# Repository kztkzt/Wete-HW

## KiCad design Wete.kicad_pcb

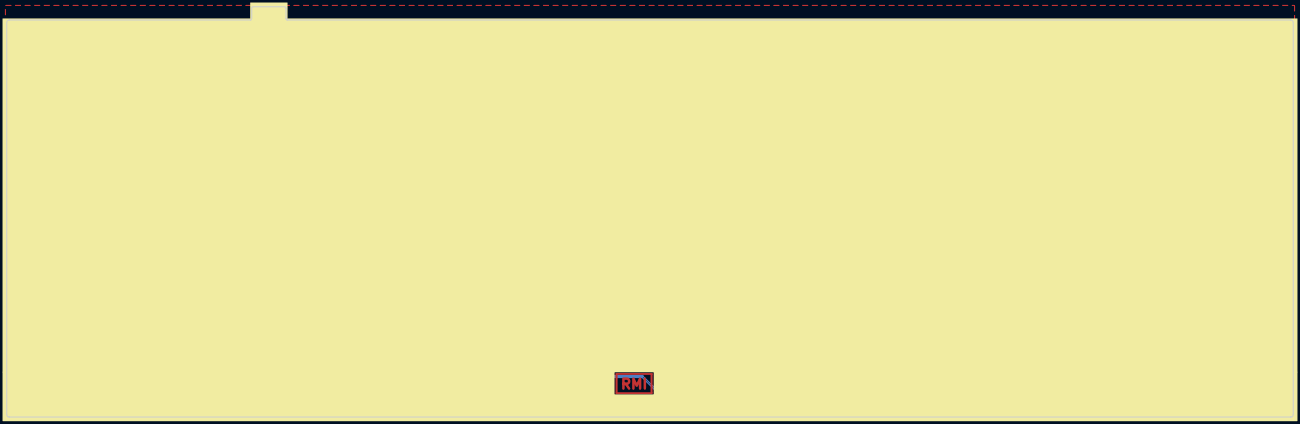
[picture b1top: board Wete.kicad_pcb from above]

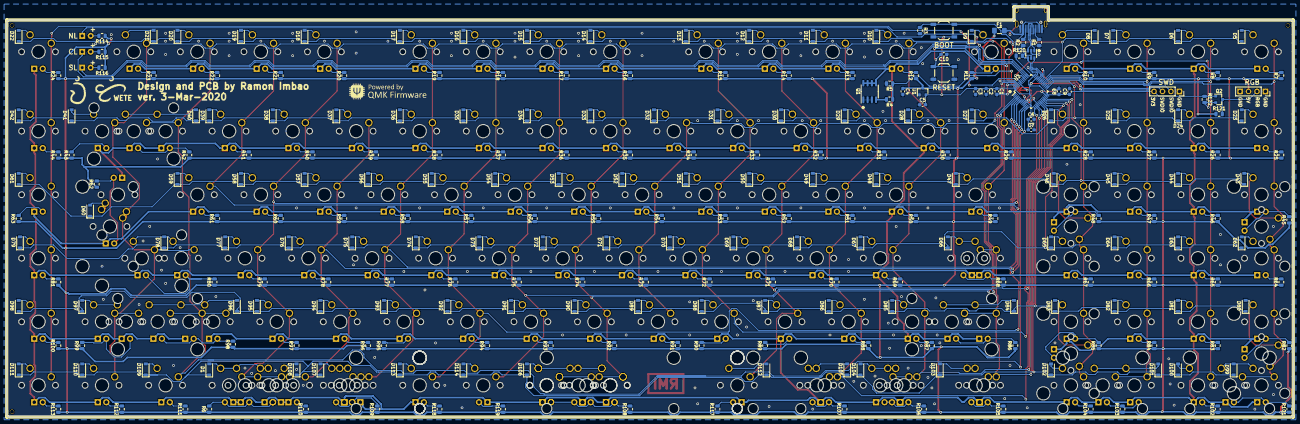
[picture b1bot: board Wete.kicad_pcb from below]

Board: 2 copper layers, 385.8 x 123.0 mm, 399 parts (254 on the bottom side), 273 nets.

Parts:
C1, C4, C8: 4.7uF; C_0603_1608Metric_Pad1.05x0.95mm_HandSolder
C2, C3, C6, C9, C10: 100nF; C_0603_1608Metric_Pad1.05x0.95mm_HandSolder
C5, C7: 1uF; C_0603_1608Metric_Pad1.05x0.95mm_HandSolder
D1, D5, D6, D7, D8, D9, D10, D11, D12, D13, D14, D15, D16, D17, D18, D19, D20, D21, D22, D23, D24, D25, D26, D27, D28, D29, D30, D31, D32, D33, D34, D35, D36, D37, D38, D39, D40, D41, D42, D43, D44, D45, D46, D47, D48, D49, D50, D51, D52, D53, D54, D55, D56, D57, D58, D59, D60, D61, D62, D63, D64, D65, D66, D67, D68, D69, D70, D71, D72, D73, D74, D75, D76, D77, D78, D79, D80, D81, D82, D83, D84, D85, D86, D87, D88, D89, D90, D91, D92, D93, D94, D95, D96, D97, D98, D99, D100, D101, D102, D103, D104, D105, D106, D107, D108, D109, D110, D111, D112, D113, D114: 1N4148; D_SOD-123-Pretty
D2, D3, D4: LED; LED_D3.0mm
F1: 500mA; C_1206_3216Metric_Pad1.42x1.75mm_HandSolder
J1, J2: Conn_01x04; PinSocket_1x04_P2.54mm_Vertical
MX1, MX2, MX3, MX4, MX5, MX6, MX7, MX8, MX9, MX10, MX11, MX12, MX13, MX14, MX15, MX16, MX17, MX18, MX20, MX21, MX22, MX23, MX24, MX25, MX26, MX27, MX28, MX29, MX30, MX31, MX32, MX33, MX34, MX35, MX36, MX37, MX38, MX39, MX43, MX44, MX45, MX46, MX48, MX49, MX50, MX51, MX52, MX53, MX54, MX55, MX56, MX57, MX58, MX59, MX61, MX63, MX64, MX65, MX66, MX68, MX69, MX70, MX71, MX72, MX73, MX74, MX75, MX76, MX77, MX78, MX80, MX84, MX85, MX86, MX87, MX89, MX90, MX91, MX92, MX93, MX94, MX95, MX96, MX97, MX98, MX99, MX101, MX102, MX113, MX114, MX115, MX116, MX123, MX124, MX125, MX126, MX129, MX132, MX136: MX-LED; MXOnly-1U-MillMax
MX19, MX40, MX41, MX81, MX82: MX-LED; MXOnly-2U-MillMax
MX42: MX-LED; MXOnly-ISO-MillMax
MX47, MX60, MX103, MX112: MX-LED; MXOnly-1.5U-MillMax
MX62, MX83, MX117, MX118, MX119, MX121, MX122: MX-LED; MXOnly-1.25U-MillMax
MX67: MX-LED; MXOnly-1.75U-FLIPPED-MillMax
MX79, MX88: MX-LED; MXOnly-2.25U-MillMax
MX100, MX133: MX-LED; MXOnly-1.75U-MillMax
MX104, MX138: MX-LED; MXOnly-7U-ReversedStabilizers-MillMax
MX105, MX106: MX-LED; MXOnly-2U-ReversedStabilizers-MillMax
MX107, MX109, MX111: MX-LED; MXOnly-1.5U-FLIPPED-MillMax
MX108, MX130, MX131, MX134, MX137, MX139: MX-LED; MXOnly-1U-FLIPPED-MillMax
MX110: MX-LED; MXOnly-6U-ReversedStabilizers-MillMax
MX120: MX-LED; MXOnly-6.25U-ReversedStabilizers-MillMax
MX127: MX-LED; MXOnly-6U-Centered-FLIPPED-ReversedStabilizers-MillMax
MX128: MX-LED; MXOnly-2.75U-MillMax
MX135: MX-LED; MXOnly-3U-ReversedStabilizers-MillMax
Q1: FDS6630A; SOIC-8_3.9x4.9mm_P1.27mm
Q2: BSS138; SOT-23
R1, R2: 5.1k; R_0805_2012Metric
R3, R5, R121, R122: 10k; R_0805_2012Metric
R4: 100; R_0805_2012Metric
R6, R7, R8, R9, R10, R11, R12, R13, R14, R15, R16, R17, R18, R19, R20, R21, R22, R23, R24, R25, R26, R27, R28, R29, R30, R31, R32, R33, R34, R35, R36, R37, R38, R39, R40, R41, R42, R43, R44, R45, R46, R47, R48, R49, R50, R51, R52, R53, R54, R55, R56, R57, R58, R59, R60, R61, R62, R63, R64, R65, R66, R67, R68, R69, R70, R71, R72, R73, R74, R75, R76, R77, R78, R79, R80, R81, R82, R83, R84, R85, R86, R87, R88, R89, R90, R91, R92, R93, R94, R95, R96, R97, R98, R99, R100, R101, R102, R103, R104, R105, R106, R107, R108, R109, R110, R111, R112, R113, R117, R118, R119: R_Small; R_0805_2012Metric
R114, R115, R116: R; R_0805_2012Metric
R120: 1.5K; R_0805_2012Metric
SW1, SW2: SW_Push; SW_SPST_TL3342
T1, T2, T3: ToolingHole; JLCPCB_ToolingHole
U1: MCP1700-3002E_SOT23; SOT-23
U2: STM32F072CBTx; LQFP-48_7x7mm_P0.5mm
U3: USBLC6-2SC6; SOT-23-6
USB1: HRO-TYPE-C-31-M-12; HRO-TYPE-C-31-M-12-HandSoldering

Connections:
+3V3: C1.1, C2.1, C3.1, C5.2, C6.1, C7.1, C8.1, C9.1, J1.4, Q2.1, R120.1, R122.1, SW2.1, U1.2, U2.9, U2.24, U2.36, U2.48
+5V: C4.1, F1.1, J2.3, R6.1, R7.1, R8.1, R9.1, R10.1, R11.1, R12.1, R13.1, R14.1, R15.1, R16.1, R17.1, R18.1, R19.1, R20.1, R21.1, R22.1, R23.1, R24.1, R25.1, R26.1, R27.1, R28.1, R29.1, R30.1, R31.1, R32.1, R33.1, R34.1, R35.1, R36.1, R37.1, R38.1, R39.1, R40.1, R41.1, R42.1, R43.1, R44.1, R45.1, R46.1, R47.1, R48.1, R49.1, R50.1, R51.1, R52.1, R53.1, R54.1, R55.1, R56.1, R57.1, R58.1, R59.1, R60.1, R61.1, R62.1, R63.1, R64.1, R65.1, R66.1, R67.1, R68.1, R69.1, R70.1, R71.1, R72.1, R73.1, R74.1, R75.1, R76.1, R77.1, R78.1, R79.1, R80.1, R81.1, R82.1, R83.1, R84.1, R85.1, R86.1, R87.1, R88.1, R89.1, R90.1, R91.1, R92.1, R93.1, R94.1, R95.1, R96.1, R97.1, R98.1, R99.1, R100.1, R101.1, R102.1, R103.1, R104.1, R105.1, R106.1, R107.1, R108.1, R109.1, R110.1, R111.1, R112.1, R113.1, R114.1, R115.1, R116.1, R117.1, R118.1, R119.1, R121.1, U1.3
BOOT0: R3.1, SW2.2, U2.44
CAPSLOCK_LED: D3.1, U2.39
COL0: MX1.1, MX20.1, MX40.1, MX43.1, MX63.1, MX81.1, MX84.1, MX105.1, MX113.1, U2.26
COL1: MX2.1, MX21.1, MX44.1, MX64.1, MX85.1, MX114.1, U2.27
COL2: MX3.1, MX22.1, MX45.1, MX65.1, MX86.1, MX106.1, MX115.1, U2.28
COL3: MX4.1, MX23.1, MX41.1, MX46.1, MX66.1, MX82.1, MX87.1, MX116.1, U2.29
COL4: MX5.1, MX24.1, MX47.1, MX62.1, MX67.1, MX83.1, MX88.1, MX107.1, MX117.1, U2.18
COL5: MX6.1, MX25.1, MX48.1, MX68.1, MX89.1, MX103.1, MX108.1, MX118.1, U2.17
COL6: MX7.1, MX26.1, MX49.1, MX69.1, MX90.1, MX109.1, MX119.1, U2.15
COL7: MX8.1, MX27.1, MX50.1, MX70.1, MX91.1, MX134.1, U2.14
COL8: MX9.1, MX28.1, MX51.1, MX71.1, MX92.1, U2.13
COL9: MX29.1, MX52.1, MX72.1, MX93.1, U2.46
COL10: MX10.1, MX30.1, MX53.1, MX73.1, MX94.1, MX104.1, MX110.1, MX120.1, MX127.1, MX135.1, MX138.1, U2.2
COL11: MX11.1, MX31.1, MX54.1, MX74.1, MX95.1, MX137.1, U2.3
COL12: MX12.1, MX32.1, MX55.1, MX75.1, MX96.1, MX136.1, U2.4
COL13: MX13.1, MX33.1, MX56.1, MX76.1, MX97.1, MX111.1, MX121.1, MX131.1, U2.5
COL14: MX34.1, MX57.1, MX77.1, MX98.1, MX129.1, U2.6
COL15: MX14.1, MX35.1, MX58.1, MX78.1, MX99.1, MX112.1, MX122.1, MX130.1, MX139.1, U2.10
COL16: MX15.1, MX36.1, MX59.1, U2.11
COL17: MX16.1, MX19.1, MX37.1, MX100.1, MX123.1, MX128.1, MX132.1, U2.12
COL18: MX17.1, MX38.1, MX42.1, MX60.2, MX79.1, MX101.1, MX124.1, MX126.1, MX133.1, U2.45
COL19: MX18.1, MX39.1, MX61.1, MX80.1, MX102.1, MX125.1, U2.43
D+: R120.2, U2.33, U3.4
D-: U2.32, U3.6
DBUS+: U3.3, USB1.6, USB1.8
DBUS-: U3.1, USB1.5, USB1.7
GND: C1.2, C2.2, C3.2, C4.2, C5.1, C6.2, C7.2, C8.2, C9.2, C10.1, J1.1, J2.1, J2.4, Q1.1, Q1.2, Q1.3, R1.1, R2.1, R3.2, R5.2, SW1.1, U1.1, U2.8, U2.23, U2.35, U2.47, U3.2, USB1.1, USB1.12, USB1.13
MOS_D: MX1.4, MX2.4, MX3.4, MX4.4, MX5.4, MX6.4, MX7.4, MX8.4, MX9.4, MX10.4, MX11.4, MX12.4, MX13.4, MX14.4, MX15.4, MX16.4, MX17.4, MX18.4, MX19.4, MX20.4, MX21.4, MX22.4, MX23.4, MX24.4, MX25.4, MX26.4, MX27.4, MX28.4, MX29.4, MX30.4, MX31.4, MX32.4, MX33.4, MX34.4, MX35.4, MX36.4, MX37.4, MX38.4, MX39.4, MX40.4, MX41.4, MX42.4, MX43.4, MX44.4, MX45.4, MX46.4, MX47.4, MX48.4, MX49.4, MX50.4, MX51.4, MX52.4, MX53.4, MX54.4, MX55.4, MX56.4, MX57.4, MX58.4, MX59.4, MX60.4, MX61.4, MX62.4, MX63.4, MX64.4, MX65.4, MX66.4, MX67.4, MX68.4, MX69.4, MX70.4, MX71.4, MX72.4, MX73.4, MX74.4, MX75.4, MX76.4, MX77.4, MX78.4, MX79.4, MX80.4, MX81.4, MX82.4, MX83.4, MX84.4, MX85.4, MX86.4, MX87.4, MX88.4, MX89.4, MX90.4, MX91.4, MX92.4, MX93.4, MX94.4, MX95.4, MX96.4, MX97.4, MX98.4, MX99.4, MX100.4, MX101.4, MX102.4, MX103.4, MX104.4, MX105.4, MX106.4, MX107.4, MX108.4, MX109.4, MX110.4, MX111.4, MX112.4, MX113.4, MX114.4, MX115.4, MX116.4, MX117.4, MX118.4, MX119.4, MX120.4, MX121.4, MX122.4, MX123.4, MX124.4, MX125.4, MX126.4, MX127.4, MX128.4, MX129.4, MX130.4, MX131.4, MX132.4, MX133.4, MX134.4, MX135.4, MX136.4, MX137.4, MX138.4, MX139.4, Q1.5, Q1.6, Q1.7, Q1.8
MOS_G: R4.1, R5.1, U2.16
NRST: C10.2, SW1.2, U2.7
NUMLOCK_LED: D2.1, U2.37
unnamed: D1.2, MX112.2, MX122.2, MX130.2, MX139.2
unnamed: D2.2, R114.2
unnamed: D3.2, R115.2
unnamed: D4.2, R116.2
unnamed: D5.2, MX1.2
unnamed: D6.2, MX2.2
unnamed: D7.2, MX3.2
unnamed: D8.2, MX4.2
unnamed: D9.2, MX5.2
unnamed: D10.2, MX6.2
unnamed: D11.2, MX7.2
unnamed: D12.2, MX8.2
unnamed: D13.2, MX9.2
unnamed: D14.2, MX10.2
unnamed: D15.2, MX11.2
unnamed: D16.2, MX12.2
unnamed: D17.2, MX13.2
unnamed: D18.2, MX14.2
unnamed: D19.2, MX15.2
unnamed: D20.2, MX16.2
unnamed: D21.2, MX17.2
unnamed: D22.2, MX18.2
unnamed: D23.2, MX20.2
unnamed: D24.2, MX21.2
unnamed: D25.2, MX22.2
unnamed: D26.2, MX23.2
unnamed: D27.2, MX24.2
unnamed: D28.2, MX25.2
unnamed: D29.2, MX26.2
unnamed: D30.2, MX27.2
unnamed: D31.2, MX28.2
unnamed: D32.2, MX29.2
unnamed: D33.2, MX30.2
unnamed: D34.2, MX31.2
unnamed: D35.2, MX32.2
unnamed: D36.2, MX33.2
unnamed: D37.2, MX34.2
unnamed: D38.2, MX35.2
unnamed: D39.2, MX36.2
unnamed: D40.2, MX19.2, MX37.2
unnamed: D41.2, MX38.2
unnamed: D42.2, MX39.2
unnamed: D43.2, MX40.2, MX43.2
unnamed: D44.2, MX44.2
unnamed: D45.2, MX45.2
unnamed: D46.2, MX41.2, MX46.2
unnamed: D47.2, MX47.2
unnamed: D48.2, MX48.2
unnamed: D49.2, MX49.2
unnamed: D50.2, MX50.2
unnamed: D51.2, MX51.2
unnamed: D52.2, MX52.2
unnamed: D53.2, MX53.2
unnamed: D54.2, MX54.2
unnamed: D55.2, MX55.2
unnamed: D56.2, MX56.2
unnamed: D57.2, MX57.2
unnamed: D58.2, MX58.2
unnamed: D59.2, MX59.2
unnamed: D60.2, MX42.2, MX60.1
unnamed: D61.2, MX61.2
unnamed: D62.2, MX63.2
unnamed: D63.2, MX64.2
unnamed: D64.2, MX65.2
unnamed: D65.2, MX66.2
unnamed: D66.2, MX62.2, MX67.2
unnamed: D67.2, MX68.2
unnamed: D68.2, MX69.2
unnamed: D69.2, MX70.2
unnamed: D70.2, MX71.2
unnamed: D71.2, MX72.2
unnamed: D72.2, MX73.2
unnamed: D73.2, MX74.2
unnamed: D74.2, MX75.2
unnamed: D75.2, MX76.2
unnamed: D76.2, MX77.2
unnamed: D77.2, MX78.2
unnamed: D78.2, MX79.2, MX126.2
unnamed: D79.2, MX80.2
unnamed: D80.2, MX81.2, MX84.2
unnamed: D81.2, MX85.2
unnamed: D82.2, MX86.2
unnamed: D83.2, MX82.2, MX87.2
unnamed: D84.2, MX83.2, MX88.2
unnamed: D85.2, MX89.2
unnamed: D86.2, MX90.2
unnamed: D87.2, MX91.2
unnamed: D88.2, MX92.2
unnamed: D89.2, MX93.2
unnamed: D90.2, MX94.2
unnamed: D91.2, MX95.2
unnamed: D92.2, MX96.2
unnamed: D93.2, MX97.2
unnamed: D94.2, MX98.2
unnamed: D95.2, MX99.2
unnamed: D96.2, MX100.2, MX128.2, MX132.2
unnamed: D97.2, MX101.2, MX133.2
unnamed: D98.2, MX102.2
unnamed: D99.2, MX105.2, MX113.2
unnamed: D100.2, MX114.2
unnamed: D101.2, MX106.2, MX115.2
unnamed: D102.2, MX116.2
unnamed: D103.2, MX107.2, MX117.2
unnamed: D104.2, MX103.2, MX108.2, MX118.2
unnamed: D105.2, MX109.2, MX119.2
unnamed: D106.2, MX104.2, MX110.2, MX120.2, MX127.2, MX135.2, MX138.2
unnamed: D107.2, MX111.2, MX121.2, MX131.2
unnamed: D108.2, MX129.2
unnamed: D109.2, MX123.2
unnamed: D110.2, MX124.2
unnamed: D111.2, MX125.2
unnamed: D112.2, MX134.2
unnamed: D113.2, MX136.2
unnamed: D114.2, MX137.2
unnamed: MX1.3, R7.2
unnamed: MX2.3, R8.2
unnamed: MX3.3, R9.2
unnamed: MX4.3, R10.2
unnamed: MX5.3, R11.2
unnamed: MX6.3, R12.2
unnamed: MX7.3, R13.2
unnamed: MX8.3, R14.2
unnamed: MX9.3, R15.2
unnamed: MX10.3, R16.2
unnamed: MX11.3, R17.2
unnamed: MX12.3, R18.2
unnamed: MX13.3, R19.2
unnamed: MX14.3, R20.2
unnamed: MX15.3, R21.2
unnamed: MX16.3, R22.2
unnamed: MX17.3, R23.2
unnamed: MX18.3, R24.2
unnamed: MX19.3, MX37.3, R42.2
unnamed: MX20.3, R25.2
unnamed: MX21.3, R26.2
unnamed: MX22.3, R27.2
unnamed: MX23.3, R28.2
unnamed: MX24.3, R29.2
unnamed: MX25.3, R30.2
unnamed: MX26.3, R31.2
unnamed: MX27.3, R32.2
unnamed: MX28.3, R33.2
unnamed: MX29.3, R34.2
unnamed: MX30.3, R35.2
unnamed: MX31.3, R36.2
unnamed: MX32.3, R37.2
unnamed: MX33.3, R38.2
unnamed: MX34.3, R39.2
unnamed: MX35.3, R40.2
unnamed: MX36.3, R41.2
unnamed: MX38.3, R43.2
unnamed: MX39.3, R44.2
unnamed: MX40.3, MX43.3, R45.2
unnamed: MX41.3, MX46.3, R48.2
unnamed: MX42.3, MX60.3, R62.2
unnamed: MX44.3, R46.2
unnamed: MX45.3, R47.2
unnamed: MX47.3, R49.2
unnamed: MX48.3, R50.2
unnamed: MX49.3, R51.2
unnamed: MX50.3, R52.2
unnamed: MX51.3, R53.2
unnamed: MX52.3, R54.2
unnamed: MX53.3, R55.2
unnamed: MX54.3, R56.2
unnamed: MX55.3, R57.2
unnamed: MX56.3, R58.2
unnamed: MX57.3, R59.2
unnamed: MX58.3, R60.2
unnamed: MX59.3, R61.2
unnamed: MX61.3, R63.2
unnamed: MX62.3, MX67.3, R68.2
unnamed: MX63.3, R64.2
unnamed: MX64.3, R65.2
unnamed: MX65.3, R66.2
unnamed: MX66.3, R67.2
unnamed: MX68.3, R69.2
unnamed: MX69.3, R70.2
unnamed: MX70.3, R71.2
unnamed: MX71.3, R72.2
unnamed: MX72.3, R73.2
unnamed: MX73.3, R74.2
unnamed: MX74.3, R75.2
unnamed: MX75.3, R76.2
unnamed: MX76.3, R77.2
unnamed: MX77.3, R78.2
unnamed: MX78.3, R79.2
unnamed: MX80.3, R81.2
unnamed: MX81.3, MX84.3, R82.2
unnamed: MX82.3, MX87.3, R85.2
unnamed: MX83.3, MX88.3, R86.2
unnamed: MX85.3, R83.2
unnamed: MX86.3, R84.2
unnamed: MX89.3, R87.2
unnamed: MX90.3, R88.2
unnamed: MX91.3, R89.2
unnamed: MX92.3, R90.2
unnamed: MX93.3, R91.2
unnamed: MX94.3, R92.2
unnamed: MX95.3, R93.2
unnamed: MX96.3, R94.2
unnamed: MX97.3, R95.2
unnamed: MX98.3, R96.2
unnamed: MX99.3, R97.2
unnamed: MX100.3, MX128.3, MX132.3, R98.2
unnamed: MX101.3, MX133.3, R99.2
unnamed: MX102.3, R100.2
unnamed: MX103.3, MX108.3, MX118.3, R106.2
unnamed: MX104.3, MX110.3, MX120.3, MX127.3, MX135.3, MX138.3, R108.2
unnamed: MX105.3, MX113.3, R101.2
unnamed: MX106.3, MX115.3, R103.2
unnamed: MX107.3, MX117.3, R105.2
unnamed: MX109.3, MX119.3, R107.2
unnamed: MX111.3, MX121.3, MX131.3, R109.2
unnamed: MX112.3, MX122.3, MX130.3, MX139.3, R6.2
unnamed: MX114.3, R102.2
unnamed: MX116.3, R104.2
unnamed: MX123.3, R111.2
unnamed: MX124.3, R112.2
unnamed: MX125.3, R113.2
unnamed: MX79.3, MX126.3, R80.2
unnamed: MX129.3, R110.2
unnamed: MX134.3, R117.2
unnamed: MX136.3, R118.2
unnamed: MX137.3, R119.2
unnamed: Q1.4, R4.2
unnamed: R1.2, USB1.4
unnamed: R2.2, USB1.10
RGB_3V3: Q2.2, R122.2, U2.40
RGB_5V: J2.2, Q2.3, R121.2
ROW0: D5.1, D6.1, D7.1, D8.1, D9.1, D10.1, D11.1, D12.1, D13.1, D14.1, D15.1, D16.1, D17.1, D18.1, D19.1, D20.1, D21.1, D22.1, U2.30
ROW1: D23.1, D24.1, D25.1, D26.1, D27.1, D28.1, D29.1, D30.1, D31.1, D32.1, D33.1, D34.1, D35.1, D36.1, D37.1, D38.1, D39.1, D40.1, D41.1, D42.1, U2.25
ROW2: D43.1, D44.1, D45.1, D46.1, D47.1, D48.1, D49.1, D50.1, D51.1, D52.1, D53.1, D54.1, D55.1, D56.1, D57.1, D58.1, D59.1, D60.1, D61.1, U2.22
ROW3: D62.1, D63.1, D64.1, D65.1, D66.1, D67.1, D68.1, D69.1, D70.1, D71.1, D72.1, D73.1, D74.1, D75.1, D76.1, D77.1, D78.1, D79.1, U2.21
ROW4: D80.1, D81.1, D82.1, D83.1, D84.1, D85.1, D86.1, D87.1, D88.1, D89.1, D90.1, D91.1, D92.1, D93.1, D94.1, D95.1, D96.1, D97.1, D98.1, U2.20
ROW5: D1.1, D99.1, D100.1, D101.1, D102.1, D103.1, D104.1, D105.1, D106.1, D107.1, D108.1, D109.1, D110.1, D111.1, D112.1, D113.1, D114.1, U2.19
SCROLLLOCK_LED: D4.1, U2.38
SWCLK: J1.2, U2.31
SWDIO: J1.3, U2.34
VCC: F1.2, U3.5, USB1.2, USB1.11

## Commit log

2020-03-26 Remove some files
